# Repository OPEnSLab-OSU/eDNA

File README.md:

# eDNA Sampler | [Updates](https://github.com/OPEnSLab-OSU/OPEnS-Lab-Home/wiki/eDNA-updates) | [Senior Design Updates](https://github.com/OPEnSLab-OSU/OPEnS-Lab-Home/wiki/eDNA-Senior-Design-Updates) | [Github](https://github.com/OPEnSLab-OSU/eDNA) | [ednaUI](https://github.com/OPEnSLab-OSU/ednaUI) | [ednaServer](https://github.com/OPEnSLab-OSU/ednaServer)

Current Project Team:

Lead: **Marc Belinga** 

Mechanical: **Hendy Kurniawan**

Software:**Marc Belinga** 

Electrical: **Reece Fitch**

## Overview

Organisms leave traces of DNA as they move through their environments. The extraction of these DNA traces is known as environmental DNA (eDNA). eDNA provides scientists and researchers with a non-invasive and sensitive way to detect and quantify species. However, traditional eDNA sampling consists of manually filtering water, which is labor and cost-intensive for remote locations. Furthermore, commercialized solutions are expensive and require a field operator. This eDNA sampler project aims to provide an affordable, open-sourced, remotely deployable, fully automated, and customizable alternative. 

## Description

The eDNA Sampler can run up to 24 inline filter units with support for different conditions including pressure, time, and volume limit. The pumps can deliver a maximum of 350mL/min of flow with each solenoid valve separating the filter housings to minimize cross-contamination. At the end of each sample, the desired stabilizing solution can be injected to fully submerge the filter for long-term storage. An optional river depth sensor can provide a proxy for flow to correct eDNA concentrations to allow for improved quantification of organisms. Data acquired during operation including water depth, pressure, temperature, and flow rate will be stored on a microSD card as a CSV file, which allows easier data export and analysis. A web application is specially designed for the eDNA Sampler for in-field programming, real-time sensor updates, scheduling tasks, and manual operations. The full sampler is estimated to be ~$6000 each.

## Field Updates
The eDNA sampler was successfully deployed in Alaska, where it operated under varying levels of turbidity and successfully collected DNA across all conditions. Over the course of six days, the sampler consistently performed three sample collections per day at multiple locations, showcasing its reliability in diverse environments. The battery capacity proved sufficient for multiple days of operation without requiring a recharge, enabling extended fieldwork in remote areas. Additionally, the sampler achieved an average margin of error of 9% in measuring water volume, demonstrating robust performance while highlighting areas for further refinement.

## Objectives

Determining the level of cross-contamination between filters during sampling.
Testing alternatives to ethanol, such as Longmire's solution, for safer and more convenient preservation during field deployments.
Improving the accuracy of water volume measurements using a tipping bucket mechanism.

| Main Control Board     |
|:-------------:|
|      | 

| Browser Application     |
|:-------------:|
|  |

## Future

Finalizing tests for Longmire’s solution to replace ethanol as the preservative.
Implementing a tipping bucket mechanism to improve measurement accuracy.

## Resource List

*  [A Build Guide for the current version (V4) of the eDNA Sampler](https://www.overleaf.com/read/rsvcsjwgfrgj) (Work in Progress)
*  [How to update an assembly in Fusion360](https://www.youtube.com/watch?v=EKoYnxrryUQ)

<!---*  [eDNA GitHub](https://github.com/OPEnSLab-OSU/eDNA)

## [eDNA Updates](https://github.com/OPEnSLab-OSU/OPEnS-Lab-Home/wiki/eDNA-updates) | [Github](https://github.com/OPEnSLab-OSU/eDNA) -->

## Problems & Solutions

Identified logistical challenges with ethanol preservation during field deployment, prompting the exploration of Longmire's solution as an alternative.
While we did average a 9% error in water volume measurements plans are currently being put in place to integrate a tipping bucket to further improve accuracy.
Continued troubleshooting to address filter clogging issues.

Feel free to contact the lab/developer if you have other ideas to solve, improve, or upgrade the eDNA sampler.

Marc Belinga: belingam@oregonstate.edu

## Keywords
eDNA, genomic, sampling, sampler, sample, environmental DNA

## Former Team Members:
Electrical: **Bao Nguyen**, **Sean Booth**,**Jacob Field**, **Kai Roy**

Programming: **Kawin Pechetratanapanit**, **Emannuel Moncada** 

Mechanical: **Torrey Menne**, **Aaron S Arvidson**, **Nikhil Wandhekar**, **Ethan Pohlschneider**, **Tilford Li**, **Danil Kryuchkov**, **Dylan Heisey**, **Joshua Iler**

## Reference
* [Types of Hydraulic Pumps](https://www.youtube.com/watch?v=Qy1iV6EzNHg)

* [eDNA AGU 2019 Poster](https://github.com/OPEnSLab-OSU/OPEnS-Hypnos/files/3996793/eDNA.poster_jsspptx.2.pdf) | [ESSOAR](https://www.essoar.org/doi/abs/10.1002/essoar.10501740.1) | 10.1002/essoar.10501740.1

*  [Inline Pressure Sensor](https://github.com/OPEnSLab-OSU/OPEnS-Lab-Home/wiki/Inline-Pressure-Sensor) (Outdated)

*  [Inline Flow Sensor](https://github.com/OPEnSLab-OSU/OPEnS-Lab-Home/wiki/IDT-Inline-Flow-Sensor) (Outdated)

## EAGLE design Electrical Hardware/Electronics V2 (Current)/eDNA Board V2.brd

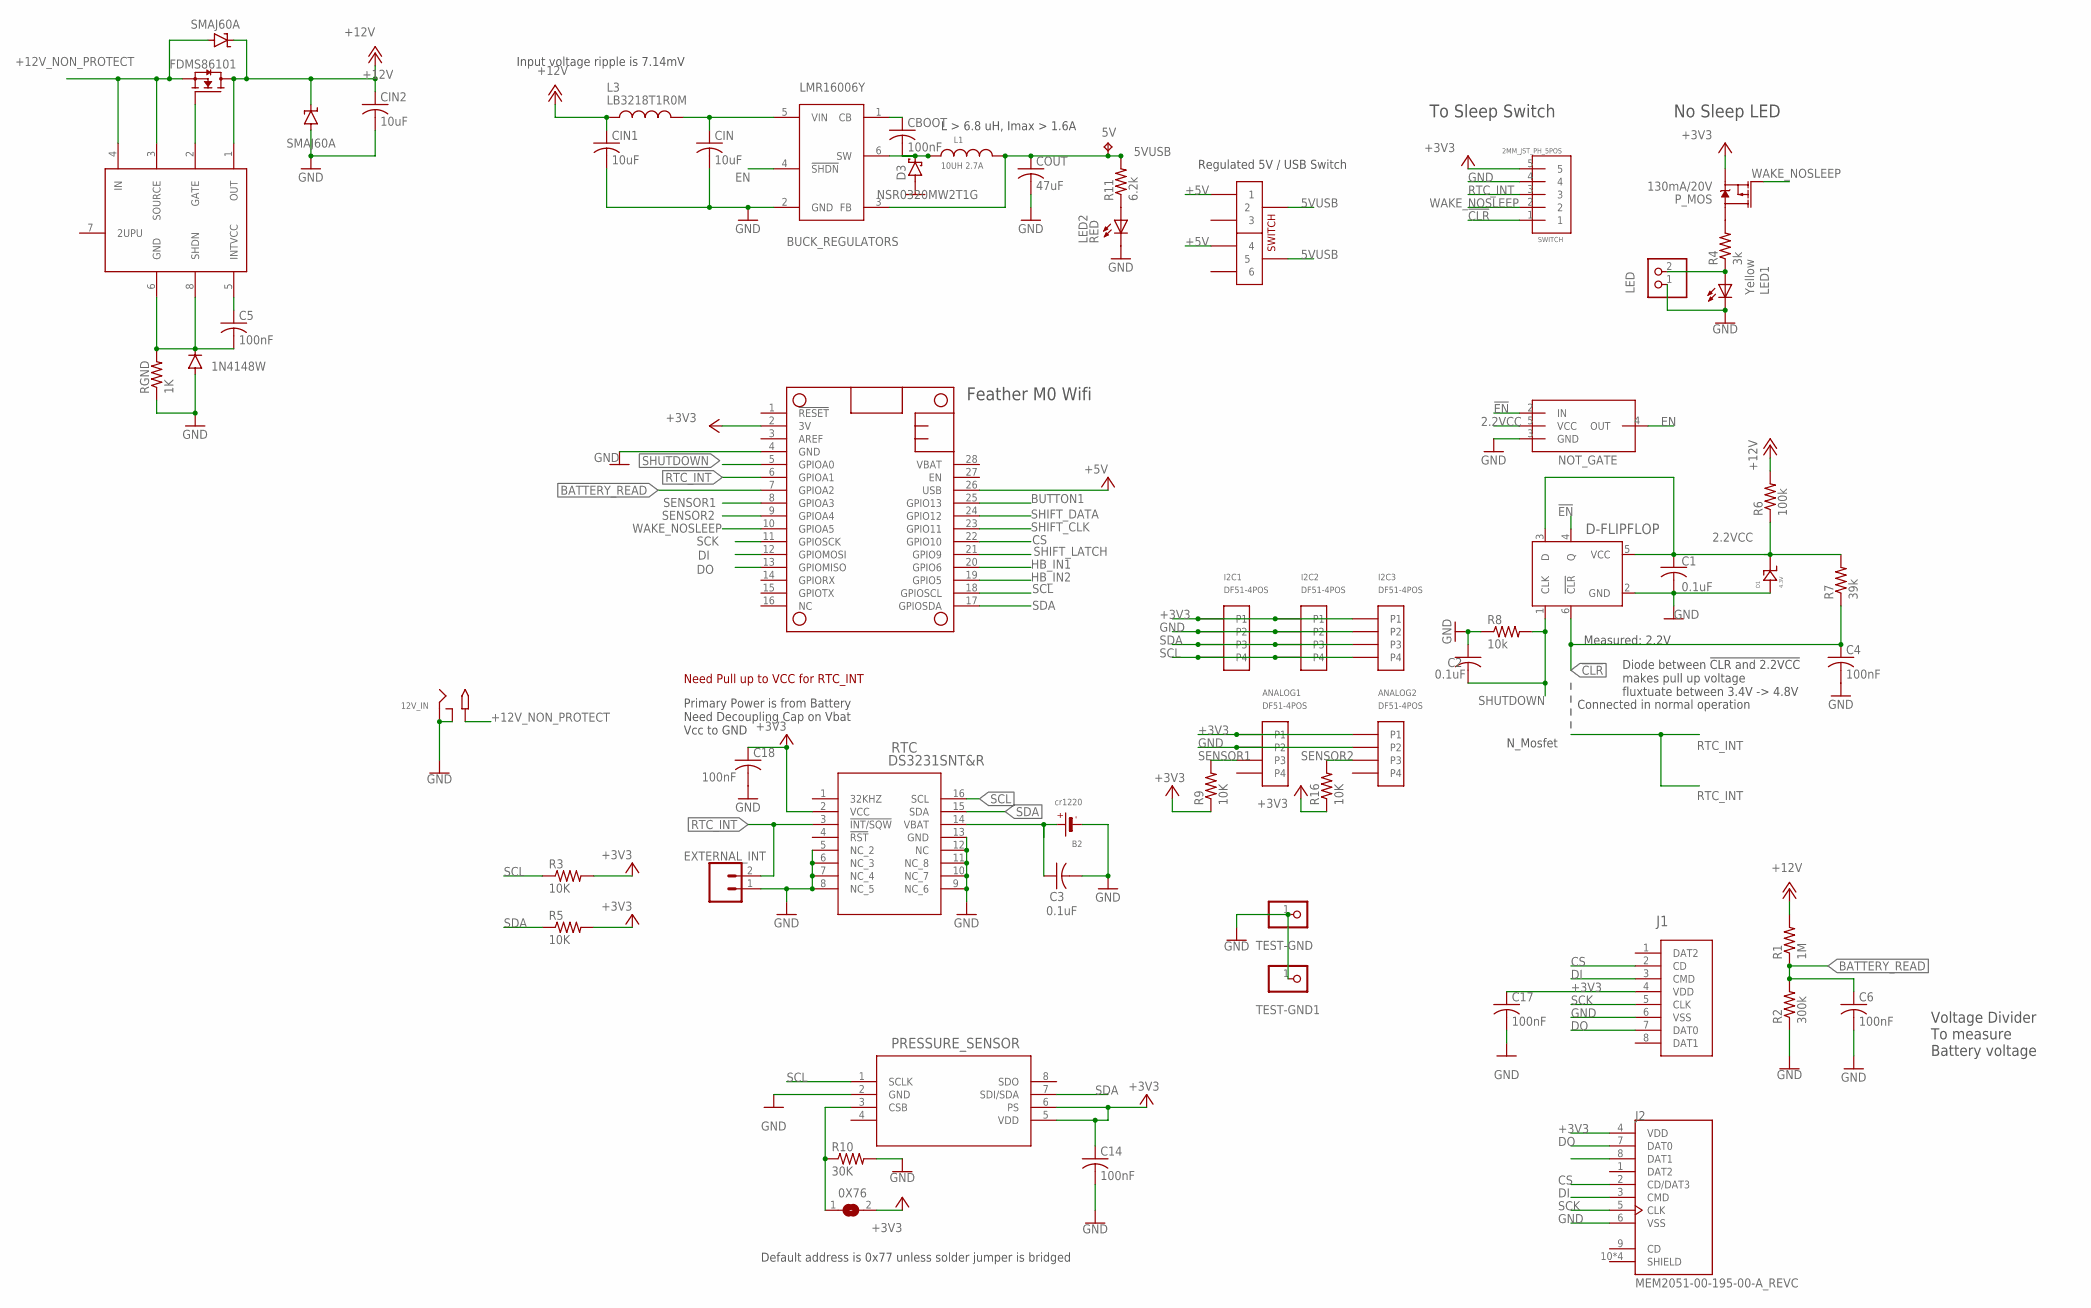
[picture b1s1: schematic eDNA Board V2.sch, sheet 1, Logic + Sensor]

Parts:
0X76: SJ
5V: TPTP16R; TP16R
12V_IN: 2.1MMJACKSMT; DCJACK_2MM_SMT
ANALOG1, ANALOG2: DF51-4POS
B2: cr1220; CR1220-2
C1, C2, C3: 0.1uF; C1206
C4, C5, C6, C14, C17, C18: 100nF; C1206
CBOOT: 100nF; C1206
CIN, CIN1, CIN2: 10uF; C1206K
COUT: 47uF; C1206
D1: 4.3V; DO-219AC
D2: 1N4148W; SOD-123_MINI-SMA
D3: NSR0320MW2T1G; SOD323_ST
D4, D5: SMAJ60A; DO_214
D-FLIPFLOP: SN74LVC1G175DBVR; DBV6
EXTERNAL_INT: CONN_021X02_NO_SILK; 1X02_NO_SILK
I2C1, I2C2, I2C3: DF51-4POS
J1: PJS008U-3000-0; CONN_PJS008U-3000-0_YAM
J2: MEM2051-00-195-00-A_REVC; GCT_MEM2051-00-195-00-A_REVC
L1: 10UH 2.7A; WE-MAPI_40XX
L3: LB3218T1R0M; INDC3218X200N
LED: 2.5MM_JST_UP_2POS; JST_2POS_2.5MM_UP
LED1: Yellow; CHIPLED_0805
LED2: RED; CHIPLED_0805
MS1: FEATHERWING
NMOS: FDMS86101; 8-POWERTDFN
PRESSURE_SENSOR: MS580302BA01-00; MS5803-02BA01
P_MOS: 130mA/20V; SOT23-3
R1: 1M; R1206
R2: 300k; R1206
R3, R5, R9, R16: 10K; R1206
R4: 3k; R1206
R6: 100k; R1206
R7: 39k; R1206
R8: 10k; R1206
R10: 30K; R1206
R11: 6.2k; RES_1206
RGND: 1K; R1206
RTC: DS3231SNT&R; 21-0042B_16
SWITCH: 2MM_JST_PH_5POS; 2MM_5POS_HEADER
TEST-GND, TEST-GND1: PINHD-1X1; 1X01
U$1: 2PDT_SWITCHJS-SMD; JS-DPDT-SMD
U$3: NOT_GATE; SOT753
U$7: LTC4372; SOP65P640X120-8N
VREG: BUCK_REGULATORS; SOT23-6

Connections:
2.2VCC: C1.1, D1.FNT, D-FLIPFLOP.3 (D), D-FLIPFLOP.5 (VCC), R6.1, R7.2, U$3.5 (VCC)
5VUSB: 5V.TP, COUT.1, L1.2, R11.2, U$1.P$2 (2), U$1.P$5 (5), VREG.3 (FB)
!CLR: C4.1, D-FLIPFLOP.6 (!CLR), R7.1, SWITCH.1
!EN: D-FLIPFLOP.4 (Q), U$3.2 (IN)
+3V3: 0X76.2, ANALOG1.P$1 (P1), ANALOG2.P$1 (P1), C14.1, C17.1, C18.1, I2C1.P$1 (P1), I2C2.P$1 (P1), I2C3.P$1 (P1), J1.4 (VDD), J2.4 (VDD), MS1.2 (3V), PRESSURE_SENSOR.5 (VDD), PRESSURE_SENSOR.6 (PS), P_MOS.2 (S), R3.2, R5.2, R9.1, R16.1, RTC.2 (VCC), SWITCH.5; also elsewhere on the board
+5V: MS1.26 (USB), U$1.P$1 (1), U$1.P$4 (4); also elsewhere on the board
+12V: CIN1.1, CIN2.1, D4.C, D5.C, L3.1, NMOS.5 (D), NMOS.6 (D), NMOS.7 (D), NMOS.8 (D), NMOS.9 (D), R1.2, R6.2, U$7.1 (OUT); also elsewhere on the board
+12V_NON_PROTECT: 12V_IN.PWR2 (TIP), D5.A, NMOS.1 (S), NMOS.2 (S), NMOS.3 (S), U$7.3 (SOURCE), U$7.4 (IN)
BATTERY_READ: C6.1, MS1.7 (GPIOA2), R1.1, R2.2
BUTTON1: MS1.25 (GPIO13)
CS: J1.2 (CD), J2.2 (CD/DAT3), MS1.22 (GPIO10)
DI: J1.3 (CMD), J2.3 (CMD), MS1.12 (GPIOMOSI)
DO: J1.7 (DAT0), J2.7 (DAT0), MS1.13 (GPIOMISO)
EN: U$3.4 (OUT), VREG.4 (!SHDN)
GND: 12V_IN.GND (RING), 12V_IN.GNDBREAK (RING_SW), ANALOG1.P$2 (P2), ANALOG2.P$2 (P2), B2.-, C1.2, C2.1, C3.2, C4.2, C6.2, C14.2, C17.2, C18.2, CIN.2, CIN1.2, CIN2.2, COUT.2, D1.BCK, D2.A, D3.A, D4.A, D-FLIPFLOP.2 (GND), EXTERNAL_INT.1, I2C1.P$2 (P2), I2C2.P$2 (P2), I2C3.P$2 (P2), J1.6 (VSS), J2.6 (VSS), LED.1, LED1.C, LED2.C, MS1.4 (GND), PRESSURE_SENSOR.2 (GND), R2.1, R8.1, R10.2, RGND.1, RTC.5 (NC_2), RTC.6 (NC_3), RTC.7 (NC_4), RTC.8 (NC_5), RTC.9 (NC_6), RTC.10 (NC_7), RTC.11 (NC_8), RTC.12 (NC), RTC.13 (GND), SWITCH.4, TEST-GND.1, TEST-GND1.1, U$3.3 (GND), VREG.2 (GND); also elsewhere on the board
HB_IN1: MS1.20 (GPIO6); also elsewhere on the board
HB_IN2: MS1.19 (GPIO5); also elsewhere on the board
unnamed: B2.+, C3.1, RTC.14 (VBAT)
unnamed: P_MOS.3 (D), R4.2
unnamed: LED.2, LED1.A, R4.1
unnamed: 0X76.1, PRESSURE_SENSOR.3 (CSB), R10.1
unnamed: NMOS.4 (G), U$7.2 (GATE)
unnamed: LED2.A, R11.1
unnamed: CIN.1, L3.2, VREG.5 (VIN)
unnamed: CBOOT.1, VREG.1 (CB)
unnamed: CBOOT.2, D3.C, L1.1, VREG.6 (SW)
unnamed: C5.1, U$7.5 (INTVCC)
unnamed: C5.2, D2.C, RGND.2, U$7.6 (GND), U$7.8 (SHDN)
RTC_INT: EXTERNAL_INT.2, MS1.6 (GPIOA1), RTC.3 (!INT/SQW), SWITCH.3
SCK: J1.5 (CLK), J2.5 (CLK), MS1.11 (GPIOSCK)
SCL: I2C1.P$4 (P4), I2C2.P$4 (P4), I2C3.P$4 (P4), MS1.18 (GPIOSCL), PRESSURE_SENSOR.1 (SCLK), R3.1, RTC.16 (SCL)
SDA: I2C1.P$3 (P3), I2C2.P$3 (P3), I2C3.P$3 (P3), MS1.17 (GPIOSDA), PRESSURE_SENSOR.7 (SDI/SDA), R5.1, RTC.15 (SDA)
SENSOR1: ANALOG1.P$3 (P3), MS1.8 (GPIOA3), R9.2
SENSOR2: ANALOG2.P$3 (P3), MS1.9 (GPIOA4), R16.2
SHIFT_CLK: MS1.23 (GPIO11); also elsewhere on the board
SHIFT_DATA: MS1.24 (GPIO12); also elsewhere on the board
SHIFT_LATCH: MS1.21 (GPIO9); also elsewhere on the board
SHUTDOWN: C2.2, D-FLIPFLOP.1 (CLK), MS1.5 (GPIOA0), R8.2
WAKE_NOSLEEP: MS1.10 (GPIOA5), P_MOS.1 (G), SWITCH.2

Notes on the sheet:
No Sleep LED
Feather M0 Wifi
To Sleep Switch
Voltage Divider To measure Battery voltage
Primary Power is from Battery Need Decoupling Cap on Vbat Vcc to GND
Measured: 2.2V
Connected in normal operation
N_Mosfet
Diode between !CLR and 2.2VCC makes pull up voltage fluxtuate between 3.4V -> 4.8V
Need Pull up to VCC for RTC_INT
Input voltage ripple is 7.14mV
L > 6.8 uH, Imax > 1.6A
Regulated 5V / USB Switch
Default address is 0x77 unless solder jumper is bridged

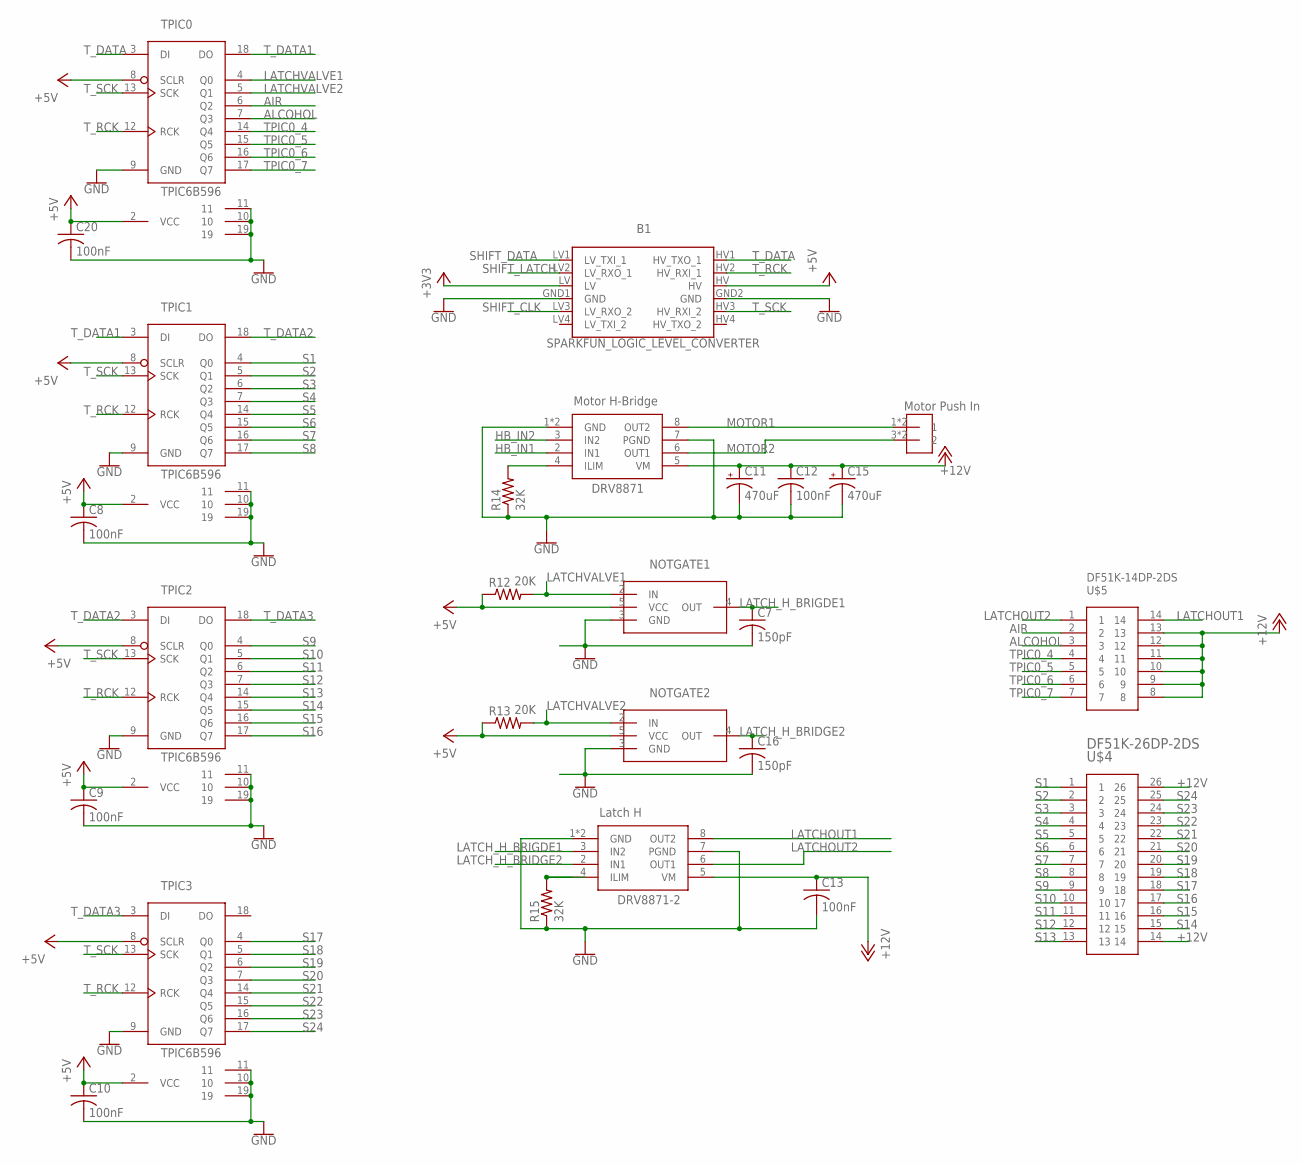
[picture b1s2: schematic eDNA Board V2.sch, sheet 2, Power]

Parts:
B1: SPARKFUN_LOGIC_LEVEL_CONVERTER
C7, C16: 150pF; C1206
C8, C9, C10, C12, C13, C20: 100nF; C1206
C11, C15: 470uF; 140CLH-0810
DRV8871: Motor H-Bridge; SOP8
DRV8871-2: Latch H; SOP8
NOTGATE1, NOTGATE2: NOT_GATE; SOT753
R12, R13: 20K; R1206
R14, R15: 32K; R1206
TPIC0, TPIC1, TPIC2, TPIC3: TPIC6B596; DIP20
U$2: Motor Push In; 3.5MM_DIP2
U$4: DF51K-26DP-2DS; DF51K-26DP-2DS-ANGLE
U$5: DF51K-14DP-2DS; DF51K-14DP-2DS-ANGLE

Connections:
+3V3: B1.LV; also elsewhere on the board
+5V: B1.HV, C8.1, C9.1, C10.1, C20.1, NOTGATE1.5 (VCC), NOTGATE2.5 (VCC), R12.1, R13.1, TPIC0.2 (VCC), TPIC0.8 (SCLR), TPIC1.2 (VCC), TPIC1.8 (SCLR), TPIC2.2 (VCC), TPIC2.8 (SCLR), TPIC3.2 (VCC), TPIC3.8 (SCLR); also elsewhere on the board
+12V: C11.+, C12.1, C13.1, C15.+, DRV8871.5 (VM), DRV8871-2.5 (VM), U$4.14, U$4.26, U$5.8, U$5.9, U$5.10, U$5.11, U$5.12, U$5.13; also elsewhere on the board
AIR: TPIC0.6 (Q2), U$5.2
ALCOHOL: TPIC0.7 (Q3), U$5.3
GND: B1.GND1 (GND), B1.GND2 (GND), C7.2, C8.2, C9.2, C10.2, C11.-, C12.2, C13.2, C15.-, C16.2, C20.2, DRV8871.1 (GND), DRV8871.7 (PGND), DRV8871.GND, DRV8871-2.1 (GND), DRV8871-2.7 (PGND), DRV8871-2.GND, NOTGATE1.3 (GND), NOTGATE2.3 (GND), R14.1, R15.1, TPIC0.9 (GND), TPIC0.10, TPIC0.11, TPIC0.19, TPIC1.9 (GND), TPIC1.10, TPIC1.11, TPIC1.19, TPIC2.9 (GND), TPIC2.10, TPIC2.11, TPIC2.19, TPIC3.9 (GND), TPIC3.10, TPIC3.11, TPIC3.19; also elsewhere on the board
HB_IN1: DRV8871.2 (IN1); also elsewhere on the board
HB_IN2: DRV8871.3 (IN2); also elsewhere on the board
LATCHOUT1: DRV8871-2.8 (OUT2), U$5.14
LATCHOUT2: DRV8871-2.6 (OUT1), U$5.1
LATCHVALVE1: NOTGATE1.2 (IN), R12.2, TPIC0.4 (Q0)
LATCHVALVE2: NOTGATE2.2 (IN), R13.2, TPIC0.5 (Q1)
LATCH_H_BRIDGE2: C16.1, DRV8871-2.2 (IN1), NOTGATE2.4 (OUT)
LATCH_H_BRIGDE1: C7.1, DRV8871-2.3 (IN2), NOTGATE1.4 (OUT)
MOTOR1: DRV8871.8 (OUT2), U$2.1, U$2.2 (1)
MOTOR2: DRV8871.6 (OUT1), U$2.3 (2), U$2.4 (2)
unnamed: DRV8871.4 (ILIM), R14.2
unnamed: DRV8871-2.4 (ILIM), R15.2
S1: TPIC1.4 (Q0), U$4.1
S2: TPIC1.5 (Q1), U$4.2
S3: TPIC1.6 (Q2), U$4.3
S4: TPIC1.7 (Q3), U$4.4
S5: TPIC1.14 (Q4), U$4.5
S6: TPIC1.15 (Q5), U$4.6
S7: TPIC1.16 (Q6), U$4.7
S8: TPIC1.17 (Q7), U$4.8
S9: TPIC2.4 (Q0), U$4.9
S10: TPIC2.5 (Q1), U$4.10
S11: TPIC2.6 (Q2), U$4.11
S12: TPIC2.7 (Q3), U$4.12
S13: TPIC2.14 (Q4), U$4.13
S14: TPIC2.15 (Q5), U$4.15
S15: TPIC2.16 (Q6), U$4.16
S16: TPIC2.17 (Q7), U$4.17
S17: TPIC3.4 (Q0), U$4.18
S18: TPIC3.5 (Q1), U$4.19
S19: TPIC3.6 (Q2), U$4.20
S20: TPIC3.7 (Q3), U$4.21
S21: TPIC3.14 (Q4), U$4.22
S22: TPIC3.15 (Q5), U$4.23
S23: TPIC3.16 (Q6), U$4.24
S24: TPIC3.17 (Q7), U$4.25
SHIFT_CLK: B1.LV3 (LV_RXO_2); also elsewhere on the board
SHIFT_DATA: B1.LV1 (LV_TXI_1); also elsewhere on the board
SHIFT_LATCH: B1.LV2 (LV_RXO_1); also elsewhere on the board
TPIC0_4: TPIC0.14 (Q4), U$5.4
TPIC0_5: TPIC0.15 (Q5), U$5.5
TPIC0_6: TPIC0.16 (Q6), U$5.6
TPIC0_7: TPIC0.17 (Q7), U$5.7
T_DATA: B1.HV1 (HV_TXO_1), TPIC0.3 (DI)
T_DATA1: TPIC0.18 (DO), TPIC1.3 (DI)
T_DATA2: TPIC1.18 (DO), TPIC2.3 (DI)
T_DATA3: TPIC2.18 (DO), TPIC3.3 (DI)
T_RCK: B1.HV2 (HV_RXI_1), TPIC0.12 (RCK), TPIC1.12 (RCK), TPIC2.12 (RCK), TPIC3.12 (RCK)
T_SCK: B1.HV3 (HV_RXI_2), TPIC0.13 (SCK), TPIC1.13 (SCK), TPIC2.13 (SCK), TPIC3.13 (SCK)

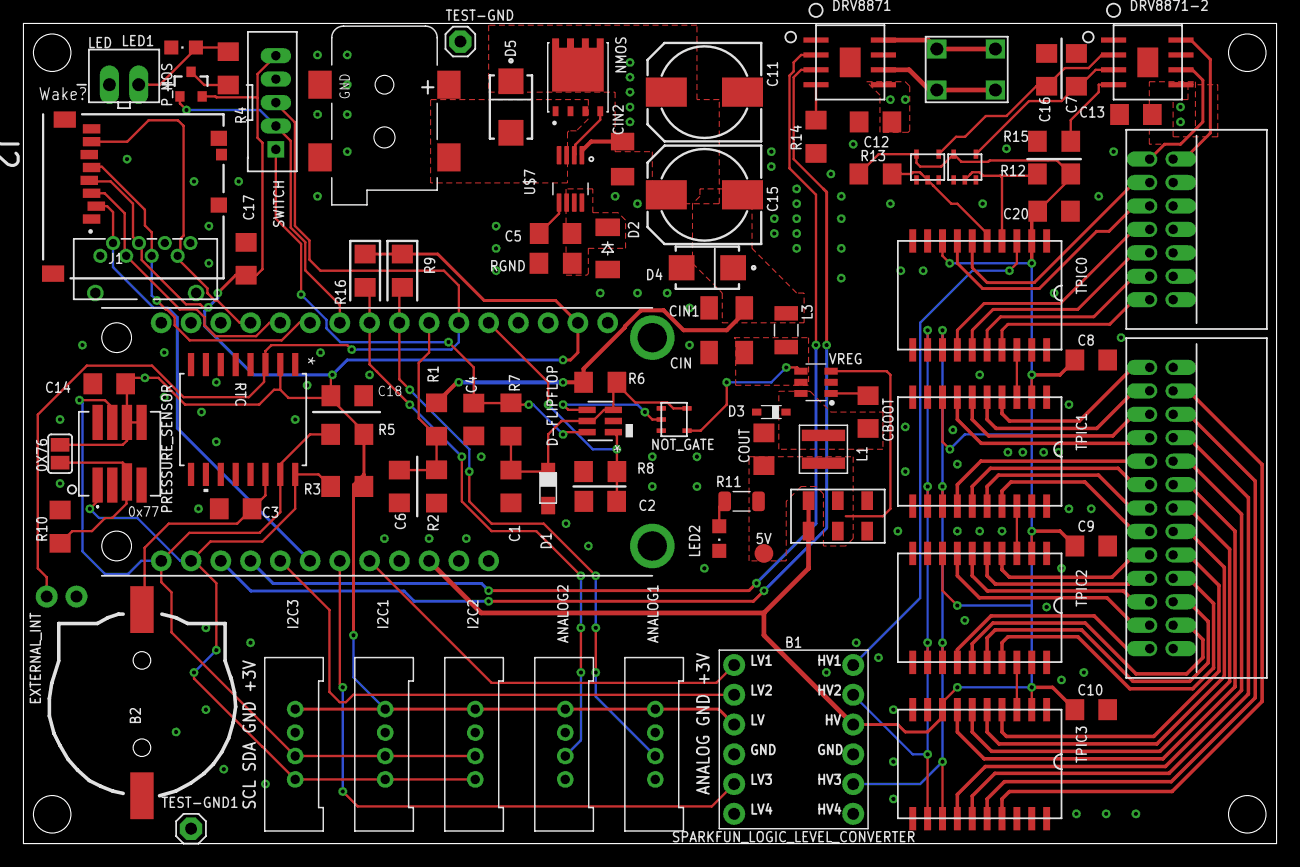
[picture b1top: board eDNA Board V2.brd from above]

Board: 2 copper layers, 107.0 x 70.0 mm, 88 parts (0 on the bottom side), 84 nets.

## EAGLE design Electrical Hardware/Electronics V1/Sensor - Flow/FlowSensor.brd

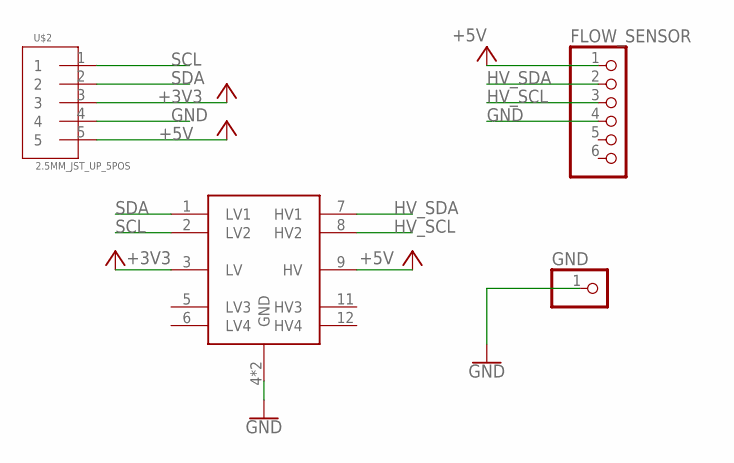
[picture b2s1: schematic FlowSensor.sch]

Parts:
FLOW_SENSOR: PINHD-1X6; 1X06
GND: PINHD-1X1; 1X01
U$1: LOGIC_LEVEL_CONVERTER
U$2: 2.5MM_JST_UP_5POS; JST_5POS_2.5MM_UP

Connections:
+3V3: U$1.3 (LV), U$2.3
+5V: FLOW_SENSOR.1, U$1.9 (HV), U$2.5
GND: FLOW_SENSOR.4, GND.1, U$1.4 (GND), U$1.10 (GND), U$2.4
HV_SCL: FLOW_SENSOR.3, U$1.8 (HV2)
HV_SDA: FLOW_SENSOR.2, U$1.7 (HV1)
SCL: U$1.2 (LV2), U$2.1
SDA: U$1.1 (LV1), U$2.2

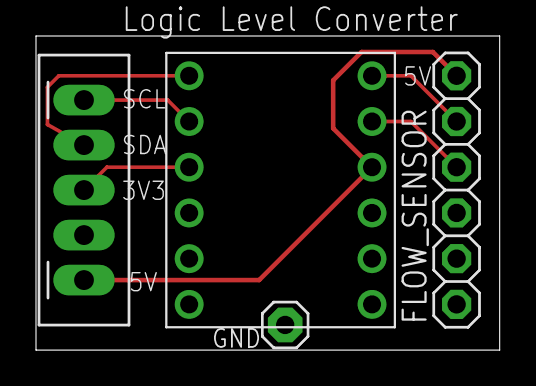
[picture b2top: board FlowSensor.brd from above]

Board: 2 copper layers, 25.8 x 17.4 mm, 4 parts (0 on the bottom side), 7 nets.

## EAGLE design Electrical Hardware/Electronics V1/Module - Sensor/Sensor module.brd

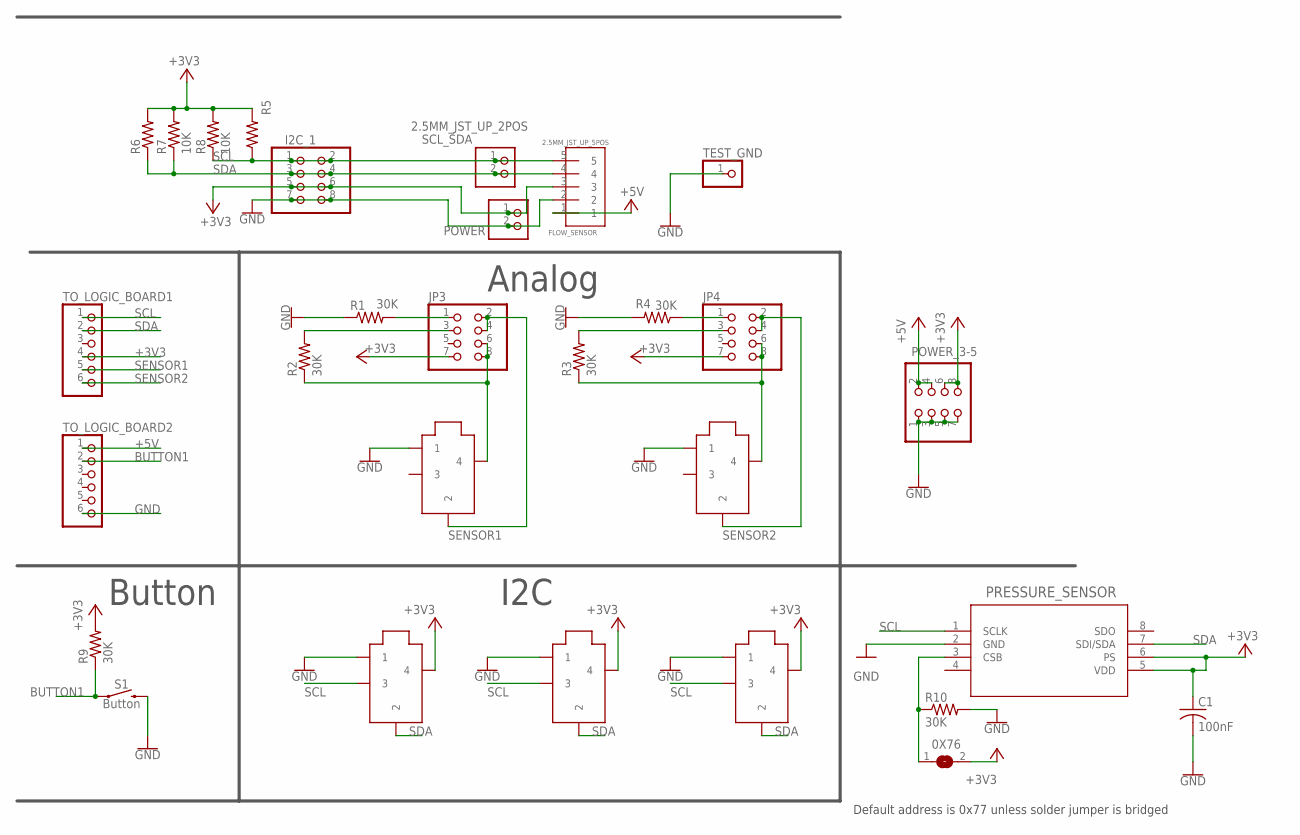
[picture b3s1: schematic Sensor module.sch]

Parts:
0X76: SJ
ANALOG1, ANALOG2: AUDIOJACK_2.5MM_SMD; AJ_2.5_SMD
C1: 100nF; C1206
FLOW_SENSOR: 2.5MM_JST_UP_5POS; JST_5POS_2.5MM_UP
I2C_1: PINHD-2X4; 2X04
JP3, JP4: PINHD-2X4; 2X04
POWER: 2.5MM_JST_UP_2POS; JST_2POS_2.5MM_UP
POWER_3-5: PINHD-2X4; 2X04
PRESSURE_SENSOR: MS580302BA01-00; MS5803-02BA01
R1, R2, R3, R4, R9, R10: 30K; R1206
R5, R6: R-US_R1206; R1206
R7, R8: 10K; 0204/7
S1: Button; TACTILE_SWITCH_PTH_6.0MM
SCL_SDA: 2.5MM_JST_UP_2POS; JST_2POS_2.5MM_UP
TEST_GND: PINHD-1X1; 1X01
TO_LOGIC_BOARD1, TO_LOGIC_BOARD2: PINHD-1X6CB; 1X06-CLEANBIG
U$1, U$2, U$5: I2C; AJ_2.5_SMD

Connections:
+3V3: 0X76.2, C1.1, FLOW_SENSOR.3, I2C_1.5, I2C_1.6, JP3.7, JP4.7, POWER.1, POWER_3-5.6, POWER_3-5.8, PRESSURE_SENSOR.5 (VDD), PRESSURE_SENSOR.6 (PS), R5.2, R6.2, R7.2, R8.2, R9.2, TO_LOGIC_BOARD1.4, U$1.4, U$2.4, U$5.4
+5V: FLOW_SENSOR.1, POWER_3-5.2, POWER_3-5.4, TO_LOGIC_BOARD2.1
BUTTON1: R9.1, S1.1, TO_LOGIC_BOARD2.2
GND: ANALOG1.1, ANALOG2.1, C1.2, FLOW_SENSOR.2, I2C_1.7, I2C_1.8, POWER.2, POWER_3-5.1, POWER_3-5.3, POWER_3-5.5, POWER_3-5.7, PRESSURE_SENSOR.2 (GND), R1.1, R4.2, R10.2, S1.3 (2), TEST_GND.1, TO_LOGIC_BOARD2.6, U$1.1, U$2.1, U$5.1
unnamed: 0X76.1, PRESSURE_SENSOR.3 (CSB), R10.1
unnamed: ANALOG1.4, JP3.6, JP3.8, R2.1
unnamed: JP3.3, R2.2
unnamed: JP3.1, R1.2
unnamed: JP4.3, R3.2
unnamed: ANALOG2.4, JP4.6, JP4.8, R3.1
unnamed: JP4.1, R4.1
SCL: FLOW_SENSOR.5, I2C_1.1, I2C_1.2, PRESSURE_SENSOR.1 (SCLK), R5.1, R8.1, SCL_SDA.1, TO_LOGIC_BOARD1.1, U$1.3, U$2.3, U$5.3
SDA: FLOW_SENSOR.4, I2C_1.3, I2C_1.4, PRESSURE_SENSOR.7 (SDI/SDA), R6.1, R7.1, SCL_SDA.2, TO_LOGIC_BOARD1.2, U$1.2, U$2.2, U$5.2
SENSOR1: ANALOG1.2, JP3.2, JP3.4, TO_LOGIC_BOARD1.5
SENSOR2: ANALOG2.2, JP4.2, JP4.4, TO_LOGIC_BOARD1.6

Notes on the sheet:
I2C
Analog
Button
Default address is 0x77 unless solder jumper is bridged

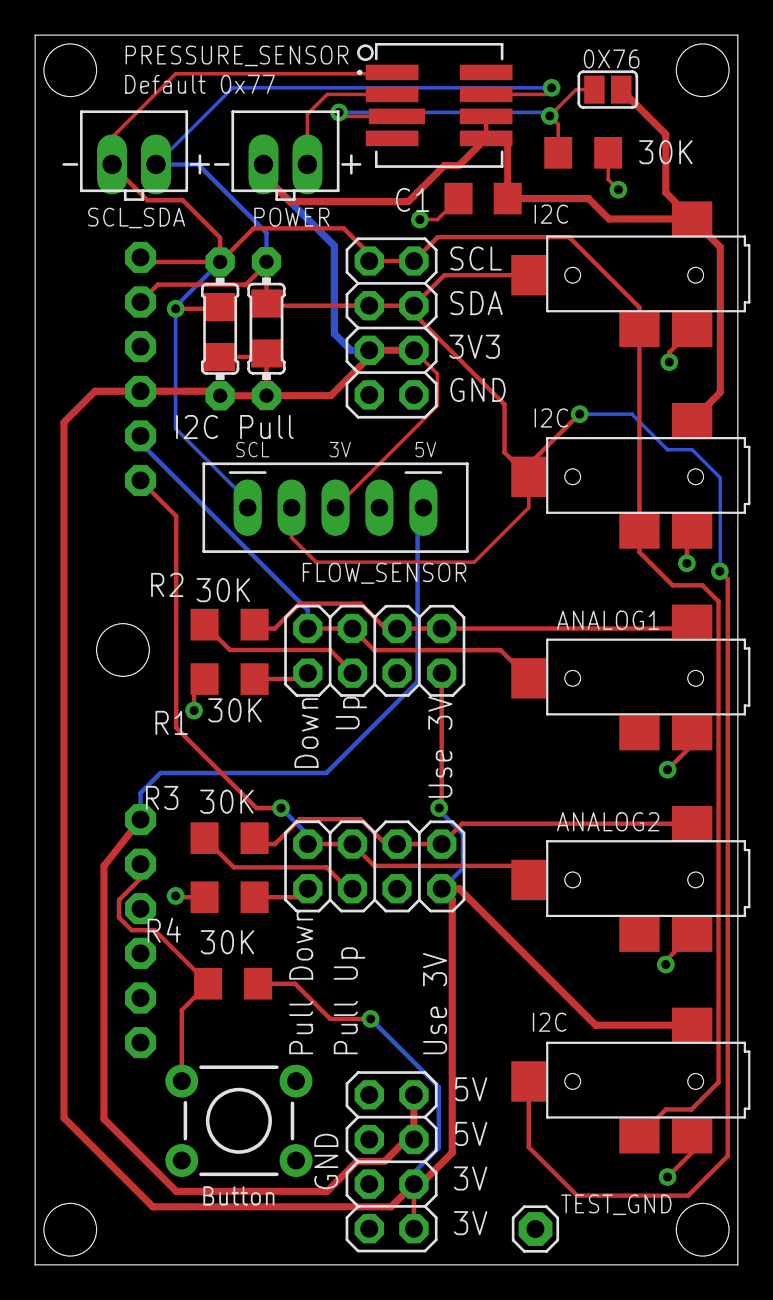
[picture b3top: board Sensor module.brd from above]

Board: 2 copper layers, 40.0 x 70.0 mm, 29 parts (0 on the bottom side), 15 nets.

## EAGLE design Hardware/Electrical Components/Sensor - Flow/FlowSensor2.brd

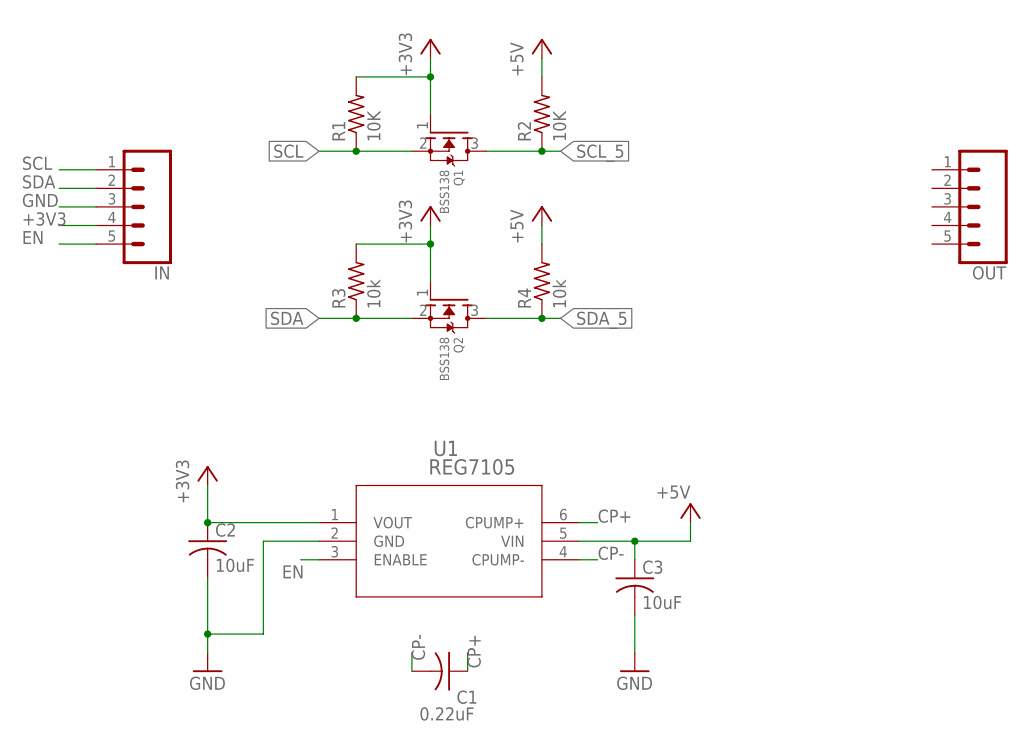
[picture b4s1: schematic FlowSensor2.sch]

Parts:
C1: 0.22uF; C0805K
C2, C3: 10uF; C0805K
IN: CONN_05PTH_LONGPADS; 1X05_LONGPADS
OUT: CONN_05PTH_LONGPADS; 1X05_LONGPADS
Q1, Q2: BSS138; SOT23
R1, R2: 10K; R1206
R3, R4: 10k; R1206
U1: REG7105; DDC6-M

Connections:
+3V3: C2.1, IN.4, Q1.1 (G), Q2.1 (G), R1.2, R3.2, U1.1 (VOUT)
+5V: C3.1, R2.2, R4.2, U1.5 (VIN)
CP+: C1.1, U1.6 (CPUMP+)
CP-: C1.2, U1.4 (CPUMP-)
EN: IN.5, U1.3 (ENABLE)
GND: C2.2, C3.2, IN.3, U1.2 (GND)
SCL: IN.1, Q1.2 (S), R1.1
SCL_5: Q1.3 (D), R2.1
SDA: IN.2, Q2.2 (S), R3.1
SDA_5: Q2.3 (D), R4.1

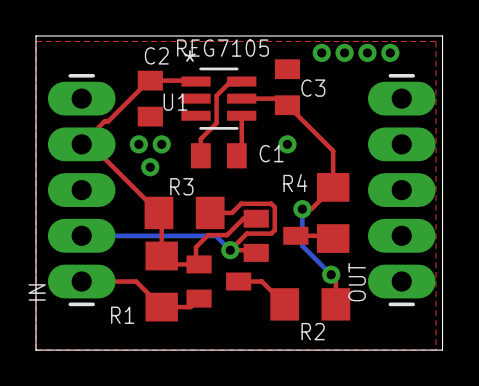
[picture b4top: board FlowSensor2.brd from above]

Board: 2 copper layers, 22.6 x 17.4 mm, 12 parts (0 on the bottom side), 10 nets.

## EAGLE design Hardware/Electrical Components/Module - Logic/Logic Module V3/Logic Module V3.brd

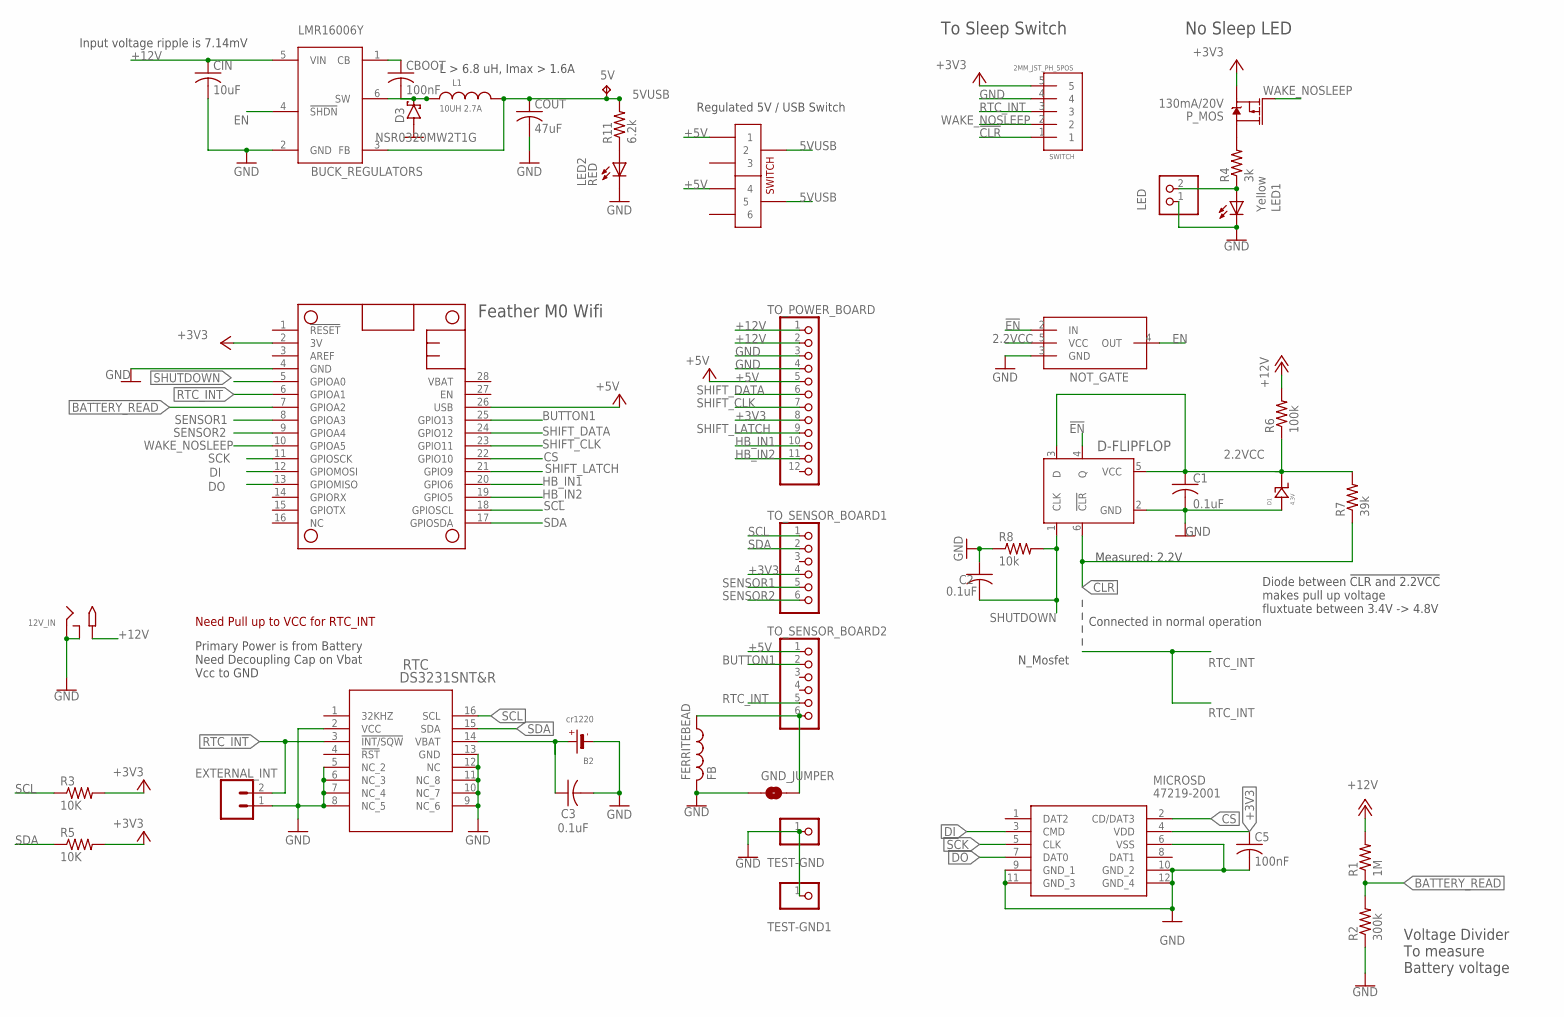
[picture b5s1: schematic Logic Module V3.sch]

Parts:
5V: TPTP16R; TP16R
12V_IN: 2.1MMJACKSMT; DCJACK_2MM_SMT
B2: cr1220; CR1220-2
C1, C2, C3: 0.1uF; C1206
C5: 100nF; C1206
CBOOT: 100nF; C1206
CIN: 10uF; C1206K
COUT: 47uF; C1206
D1: 4.3V; DO-219AC
D3: NSR0320MW2T1G; SOD323_ST
D-FLIPFLOP: SN74LVC1G175DBVR; DBV6
EXTERNAL_INT: CONN_021X02_NO_SILK; 1X02_NO_SILK
FERRITEBEAD: FB
GND_JUMPER: JUMPER-SMT_2_NO_NO-SILK; SMT-JUMPER_2_NO_NO-SILK
L1: 10UH 2.7A; WE-MAPI_40XX
LED: 2.5MM_JST_UP_2POS; JST_2POS_2.5MM_UP
LED1: Yellow; CHIPLED_0805
LED2: RED; CHIPLED_0805
MICROSD: 47219-2001; 472192001
MS1: FEATHERWING
P_MOS: 130mA/20V; SOT23-3
R1: 1M; R1206
R2: 300k; R1206
R3, R5: 10K; R1206
R4: 3k; R1206
R6: 100k; R1206
R7: 39k; R1206
R8: 10k; R1206
R11: 6.2k; RES_1206
RTC: DS3231SNT&R; 21-0042B_16
SWITCH: 2MM_JST_PH_5POS; 2MM_5POS_HEADER
TEST-GND, TEST-GND1: PINHD-1X1; 1X01
TO_POWER_BOARD: PINHD-1X12; 1X12
TO_SENSOR_BOARD1, TO_SENSOR_BOARD2: PINHD-1X6CB; 1X06-CLEANBIG
U$1: 2PDT_SWITCHJS-SMD; JS-DPDT-SMD
U$3: NOT_GATE; SOT753
VREG: BUCK_REGULATORS; SOT23-6

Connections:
2.2VCC: C1.1, D1.FNT, D-FLIPFLOP.3 (D), D-FLIPFLOP.5 (VCC), R6.1, R7.2, U$3.5 (VCC)
5VUSB: 5V.TP, COUT.1, L1.2, R11.2, U$1.P$2 (2), U$1.P$5 (5), VREG.3 (FB)
!CLR: D-FLIPFLOP.6 (!CLR), R7.1, SWITCH.1
!EN: D-FLIPFLOP.4 (Q), U$3.2 (IN)
+3V3: C5.1, MICROSD.4 (VDD), MS1.2 (3V), P_MOS.2 (S), R3.2, R5.2, SWITCH.5, TO_POWER_BOARD.8, TO_SENSOR_BOARD1.4
+5V: MS1.26 (USB), TO_POWER_BOARD.5, TO_SENSOR_BOARD2.1, U$1.P$1 (1), U$1.P$4 (4)
+12V: 12V_IN.PWR2 (TIP), CIN.1, R1.2, R6.2, TO_POWER_BOARD.1, TO_POWER_BOARD.2, VREG.5 (VIN)
BATTERY_READ: MS1.7 (GPIOA2), R1.1, R2.2
BUTTON1: MS1.25 (GPIO13), TO_SENSOR_BOARD2.2
CS: MICROSD.2 (CD/DAT3), MS1.22 (GPIO10)
DI: MICROSD.3 (CMD), MS1.12 (GPIOMOSI)
DO: MICROSD.7 (DAT0), MS1.13 (GPIOMISO)
EN: U$3.4 (OUT), VREG.4 (!SHDN)
GND: 12V_IN.GND (RING), 12V_IN.GNDBREAK (RING_SW), B2.-, C1.2, C2.1, C3.2, C5.2, CIN.2, COUT.2, D1.BCK, D3.A, D-FLIPFLOP.2 (GND), EXTERNAL_INT.1, FERRITEBEAD.P$2 (2), GND_JUMPER.1, LED.1, LED1.C, LED2.C, MICROSD.6 (VSS), MICROSD.9 (GND_1), MICROSD.10 (GND_2), MICROSD.11 (GND_3), MICROSD.12 (GND_4), MS1.4 (GND), R2.1, R8.1, RTC.2 (VCC), RTC.5 (NC_2), RTC.6 (NC_3), RTC.7 (NC_4), RTC.8 (NC_5), RTC.9 (NC_6), RTC.10 (NC_7), RTC.11 (NC_8), RTC.12 (NC), RTC.13 (GND), SWITCH.4, TEST-GND.1, TEST-GND1.1, TO_POWER_BOARD.3, TO_POWER_BOARD.4, U$3.3 (GND), VREG.2 (GND)
HB_IN1: MS1.20 (GPIO6), TO_POWER_BOARD.10
HB_IN2: MS1.19 (GPIO5), TO_POWER_BOARD.11
unnamed: B2.+, C3.1, RTC.14 (VBAT)
unnamed: P_MOS.3 (D), R4.2
unnamed: LED.2, LED1.A, R4.1
unnamed: FERRITEBEAD.P$1 (1), GND_JUMPER.2, TO_SENSOR_BOARD2.6
unnamed: LED2.A, R11.1
unnamed: CBOOT.1, VREG.1 (CB)
unnamed: CBOOT.2, D3.C, L1.1, VREG.6 (SW)
RTC_INT: EXTERNAL_INT.2, MS1.6 (GPIOA1), RTC.3 (!INT/SQW), SWITCH.3, TO_SENSOR_BOARD2.5
SCK: MICROSD.5 (CLK), MS1.11 (GPIOSCK)
SCL: MS1.18 (GPIOSCL), R3.1, RTC.16 (SCL), TO_SENSOR_BOARD1.1
SDA: MS1.17 (GPIOSDA), R5.1, RTC.15 (SDA), TO_SENSOR_BOARD1.2
SENSOR1: MS1.8 (GPIOA3), TO_SENSOR_BOARD1.5
SENSOR2: MS1.9 (GPIOA4), TO_SENSOR_BOARD1.6
SHIFT_CLK: MS1.23 (GPIO11), TO_POWER_BOARD.7
SHIFT_DATA: MS1.24 (GPIO12), TO_POWER_BOARD.6
SHIFT_LATCH: MS1.21 (GPIO9), TO_POWER_BOARD.9
SHUTDOWN: C2.2, D-FLIPFLOP.1 (CLK), MS1.5 (GPIOA0), R8.2
WAKE_NOSLEEP: MS1.10 (GPIOA5), P_MOS.1 (G), SWITCH.2

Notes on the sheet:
No Sleep LED
Feather M0 Wifi
To Sleep Switch
Voltage Divider To measure Battery voltage
Primary Power is from Battery Need Decoupling Cap on Vbat Vcc to GND
Measured: 2.2V
Connected in normal operation
N_Mosfet
Diode between !CLR and 2.2VCC makes pull up voltage fluxtuate between 3.4V -> 4.8V
Input voltage ripple is 7.14mV
L > 6.8 uH, Imax > 1.6A
Regulated 5V / USB Switch
Need Pull up to VCC for RTC_INT

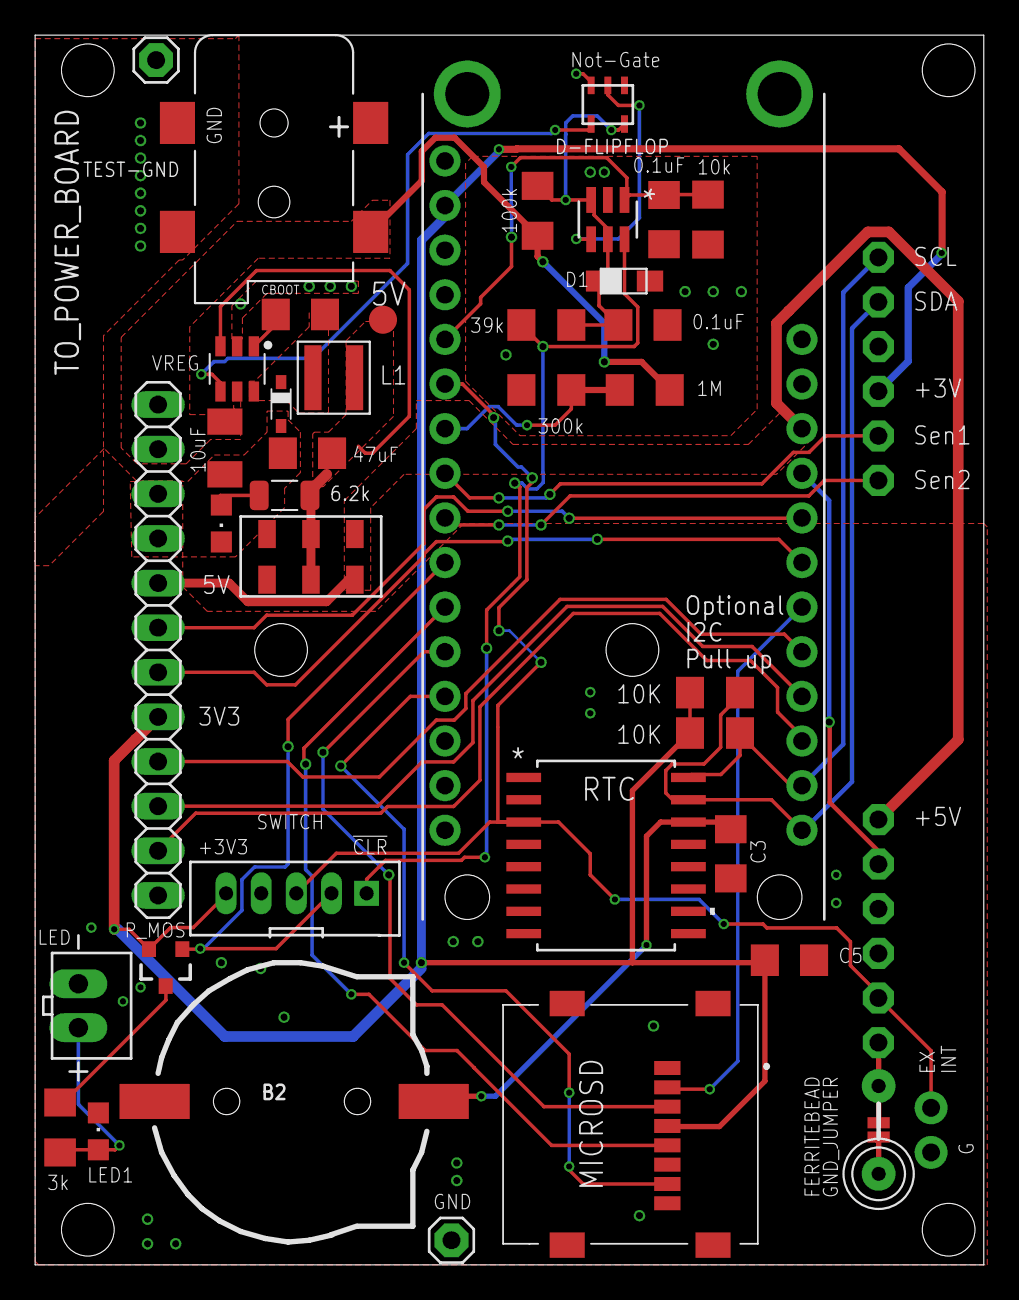
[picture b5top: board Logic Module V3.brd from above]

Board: 2 copper layers, 54.0 x 70.0 mm, 43 parts (1 on the bottom side), 34 nets.

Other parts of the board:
U$2: OPENS-LOGO

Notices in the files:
parts and their libraries:
SparkFun-Boards: Licensing: Creative Commons ShareAlike 4.0 International - https://creativecommons.org/licenses/by-sa/4.0
microbuilder: This work is placed in the public domain, and may be freely used for commercial and non-commercial work with the following conditions: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
